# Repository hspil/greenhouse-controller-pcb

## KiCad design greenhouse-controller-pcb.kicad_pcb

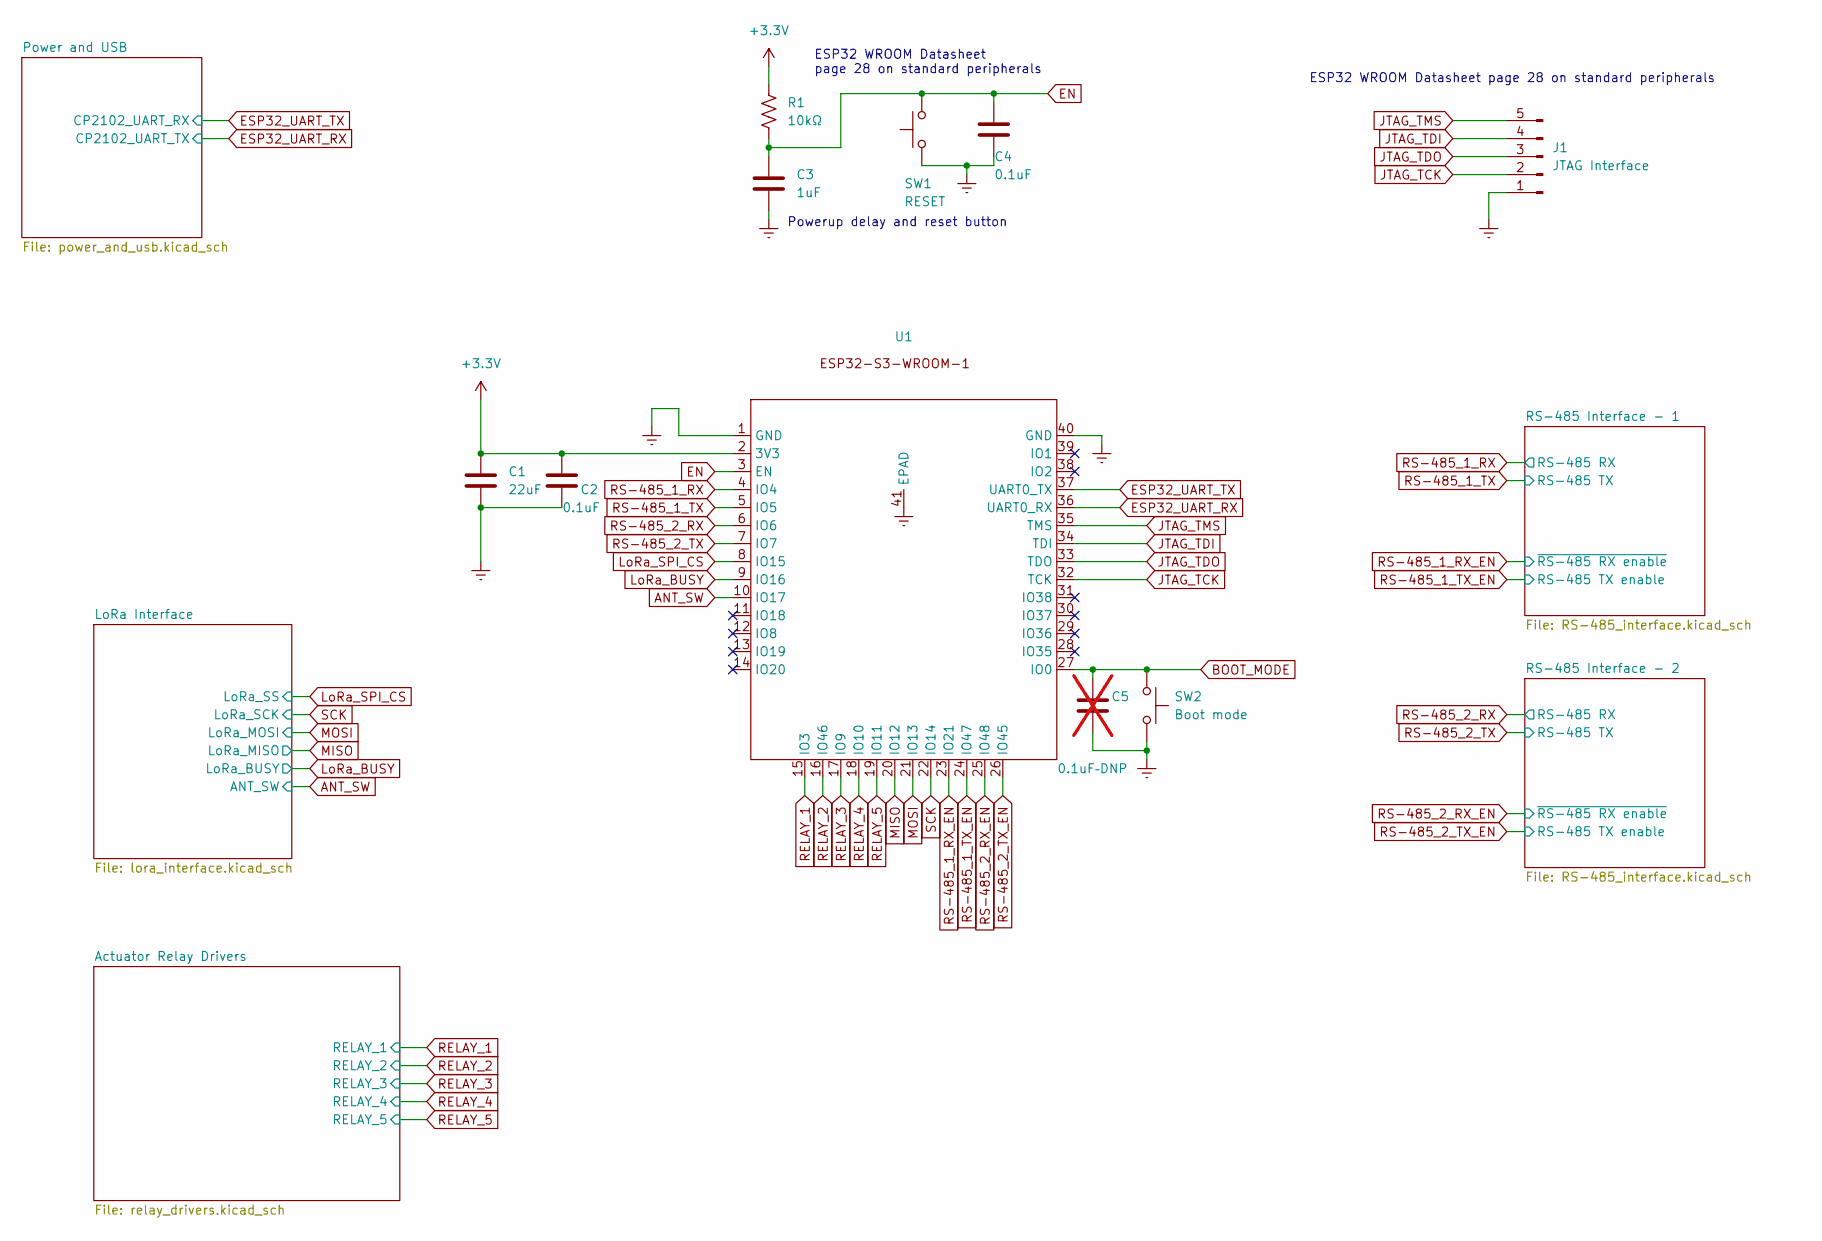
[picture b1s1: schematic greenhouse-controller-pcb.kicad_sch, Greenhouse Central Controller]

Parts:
C1: 22uF; C_0805_2012Metric_Pad1.18x1.45mm_HandSolder
C2, C4: 0.1uF; C_0805_2012Metric_Pad1.18x1.45mm_HandSolder
C3: 1uF; C_0805_2012Metric_Pad1.18x1.45mm_HandSolder
C5: 0.1uF–DNP; not fitted
J1: JTAG Interface; PinSocket_1x05_P2.54mm_Vertical
R1: 10kΩ; R_0805_2012Metric_Pad1.20x1.40mm_HandSolder
SW1: RESET; SW4_PTS815 SJM 250 SMTR LFS_CNK
SW2: Boot mode; SW4_PTS815 SJM 250 SMTR LFS_CNK
U1: ESP32-S3-WROOM-1_EXP

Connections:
+3.3V: C1.1, C2.1, R1.1, U1.2 (3V3); also elsewhere on the board
ANT_SW: U1.10 (IO17); also elsewhere on the board
BOOT_MODE: C5.1, SW2.1, U1.27 (IO0); also elsewhere on the board
ESP32_UART_RX: U1.36 (UART0_RX); also elsewhere on the board
ESP32_UART_TX: U1.37 (UART0_TX); also elsewhere on the board
JTAG_TCK: J1.2, U1.32 (TCK)
JTAG_TDI: J1.4, U1.34 (TDI)
JTAG_TDO: J1.3, U1.33 (TDO)
JTAG_TMS: J1.5, U1.35 (TMS)
LoRa_BUSY: U1.9 (IO16); also elsewhere on the board
LoRa_SPI_CS: U1.8 (IO15); also elsewhere on the board
MISO: U1.20 (IO12); also elsewhere on the board
MOSI: U1.21 (IO13); also elsewhere on the board
RELAY_1: U1.15 (IO3); also elsewhere on the board
RELAY_2: U1.16 (IO46); also elsewhere on the board
RELAY_3: U1.17 (IO9); also elsewhere on the board
RELAY_4: U1.18 (IO10); also elsewhere on the board
RELAY_5: U1.19 (IO11); also elsewhere on the board
RS-485_1_RX: U1.4 (IO4); also elsewhere on the board
RS-485_1_RX_EN: U1.23 (IO21); also elsewhere on the board
RS-485_1_TX: U1.5 (IO5); also elsewhere on the board
RS-485_1_TX_EN: U1.24 (IO47); also elsewhere on the board
RS-485_2_RX: U1.6 (IO6); also elsewhere on the board
RS-485_2_RX_EN: U1.25 (IO48); also elsewhere on the board
RS-485_2_TX: U1.7 (IO7); also elsewhere on the board
RS-485_2_TX_EN: U1.26 (IO45); also elsewhere on the board
SCK: U1.22 (IO14); also elsewhere on the board

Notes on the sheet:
Powerup delay and reset button
ESP32 WROOM Datasheet page 28 on standard peripherals
ESP32 WROOM Datasheet page 28 on standard peripherals

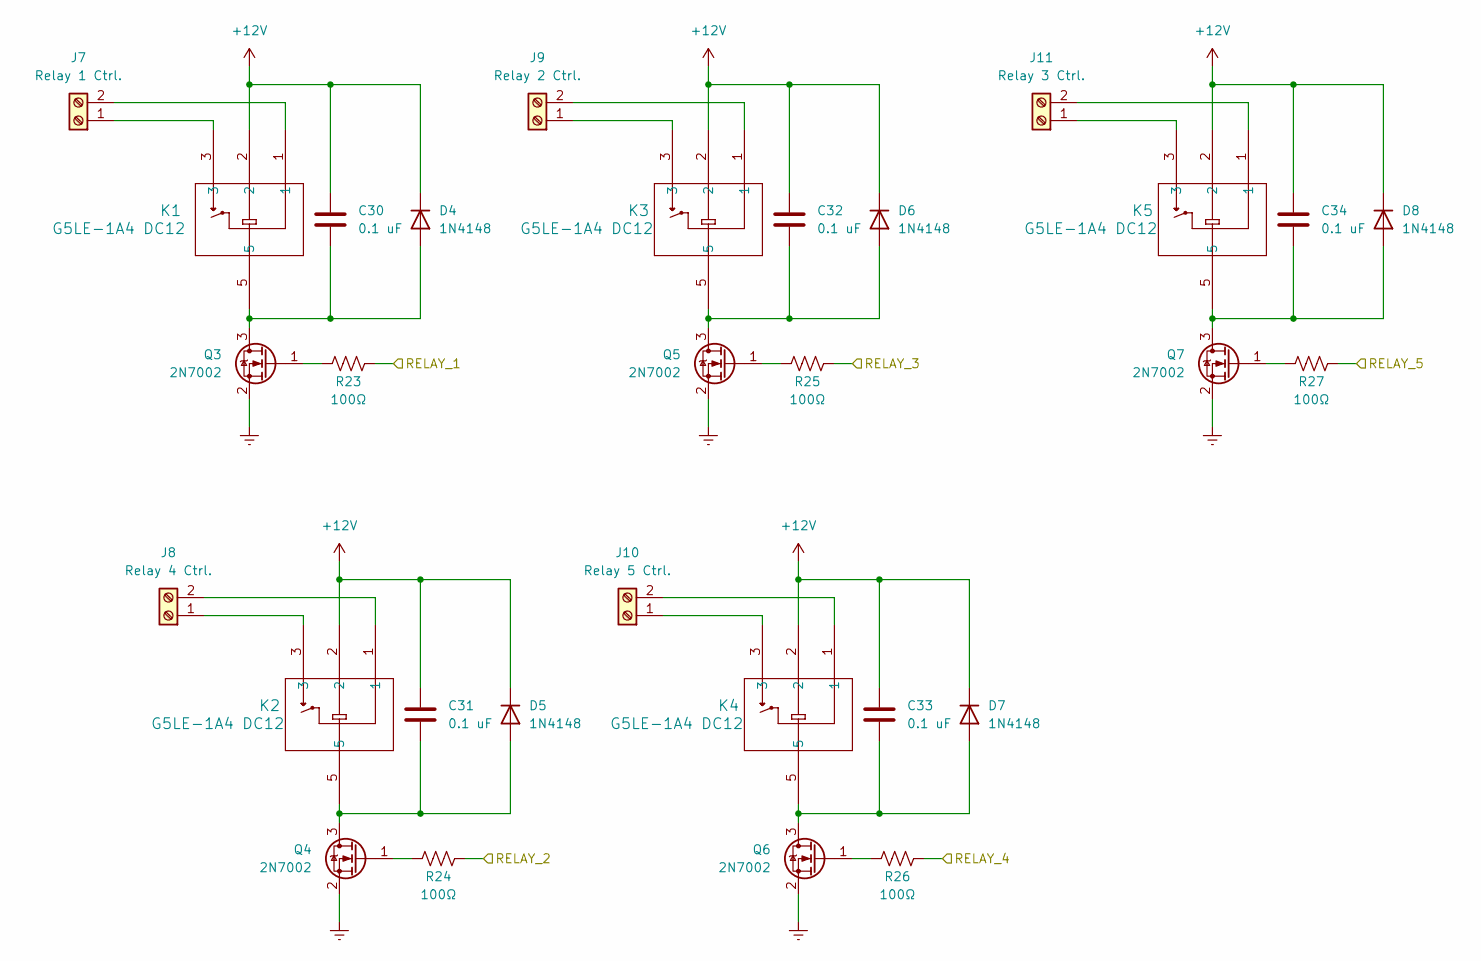
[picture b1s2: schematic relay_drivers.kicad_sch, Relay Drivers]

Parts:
C30, C31, C32, C33, C34: 0.1 uF; C_0805_2012Metric_Pad1.18x1.45mm_HandSolder
D4, D5, D6, D7, D8: 1N4148; D_DO-35_SOD27_P7.62mm_Horizontal
J7: Relay 1 Ctrl.; CUI_TB007-508-02BE
J8: Relay 4 Ctrl.; CUI_TB007-508-02BE
J9: Relay 2 Ctrl.; CUI_TB007-508-02BE
J10: Relay 5 Ctrl.; CUI_TB007-508-02BE
J11: Relay 3 Ctrl.; CUI_TB007-508-02BE
K1, K2, K3, K4, K5: G5LE-1A4 DC12; RELAY_G5LE-1A DC5_OMR
Q3, Q4, Q5, Q6, Q7: 2N7002; SOT-23
R23, R24, R25, R26, R27: 100Ω; R_0805_2012Metric_Pad1.20x1.40mm_HandSolder

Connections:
+12V: C30.1, C31.1, C32.1, C33.1, C34.1, D4.1 (K), D5.1 (K), D6.1 (K), D7.1 (K), D8.1 (K), K1.2, K2.2, K3.2, K4.2, K5.2; also elsewhere on the board
unnamed: C30.2, D4.2 (A), K1.5, Q3.3 (D)
unnamed: C31.2, D5.2 (A), K2.5, Q4.3 (D)
unnamed: C32.2, D6.2 (A), K3.5, Q5.3 (D)
unnamed: C33.2, D7.2 (A), K4.5, Q6.3 (D)
unnamed: C34.2, D8.2 (A), K5.5, Q7.3 (D)
unnamed: J7.1, K1.3
unnamed: J7.2, K1.1
unnamed: J8.1, K2.3
unnamed: J8.2, K2.1
unnamed: J9.1, K3.3
unnamed: J9.2, K3.1
unnamed: J10.1, K4.3
unnamed: J10.2, K4.1
unnamed: J11.1, K5.3
unnamed: J11.2, K5.1
unnamed: Q3.1 (G), R23.2
unnamed: Q4.1 (G), R24.1
unnamed: Q5.1 (G), R25.1
unnamed: Q6.1 (G), R26.1
unnamed: Q7.1 (G), R27.1
RELAY_1: R23.1; also elsewhere on the board
RELAY_2: R24.2; also elsewhere on the board
RELAY_3: R25.2; also elsewhere on the board
RELAY_4: R26.2; also elsewhere on the board
RELAY_5: R27.2; also elsewhere on the board

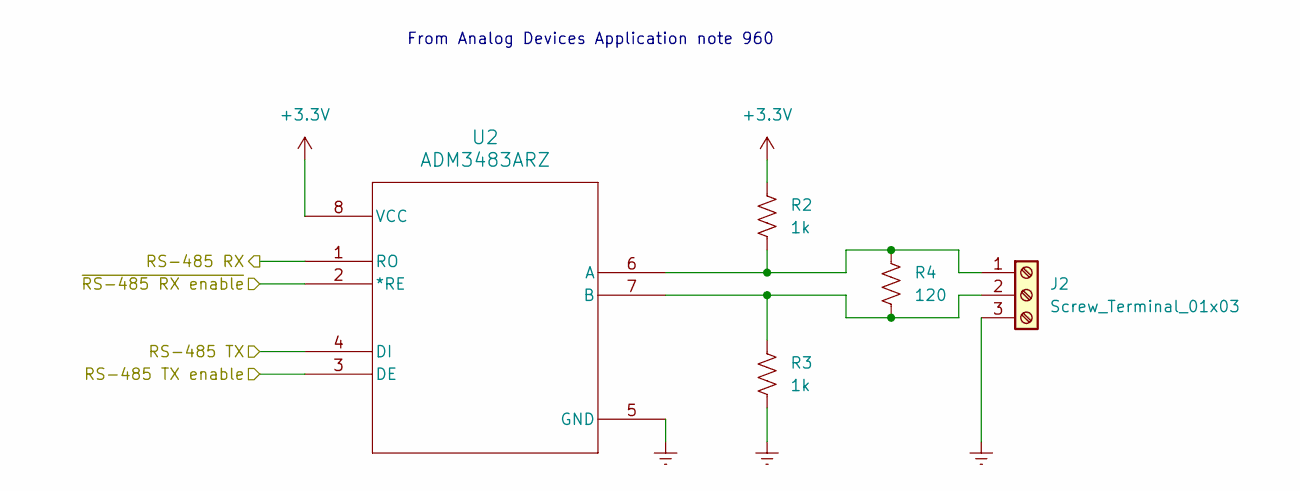
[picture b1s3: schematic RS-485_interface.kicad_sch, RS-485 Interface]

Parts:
J2: Screw_Terminal_01x03; CUI_TB007-508-03BE
R2, R3: 1k; R_0805_2012Metric_Pad1.20x1.40mm_HandSolder
R4: 120; R_Axial_DIN0207_L6.3mm_D2.5mm_P7.62mm_Horizontal
U2: ADM3483ARZ; R_8_ADI

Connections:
+3.3V: R2.1, U2.8 (VCC); also elsewhere on the board
unnamed: J2.1, R2.2, R4.1, U2.6 (A)
unnamed: J2.2, R3.1, R4.2, U2.7 (B)
RS-485_1_RX: U2.1 (RO); also elsewhere on the board
RS-485_1_RX_EN: U2.2 (*RE); also elsewhere on the board
RS-485_1_TX: U2.4 (DI); also elsewhere on the board
RS-485_1_TX_EN: U2.3 (DE); also elsewhere on the board

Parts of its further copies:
J3: Screw_Terminal_01x03; CUI_TB007-508-03BE
R5, R6: 1k; R_0805_2012Metric_Pad1.20x1.40mm_HandSolder
R7: 120; R_Axial_DIN0207_L6.3mm_D2.5mm_P7.62mm_Horizontal
U3: ADM3483ARZ; R_8_ADI

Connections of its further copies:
+3.3V: R5.1, U3.8 (VCC); also elsewhere on the board
unnamed: J3.1, R5.2, R7.1, U3.6 (A)
unnamed: J3.2, R6.1, R7.2, U3.7 (B)
RS-485_2_RX: U3.1 (RO); also elsewhere on the board
RS-485_2_RX_EN: U3.2 (*RE); also elsewhere on the board
RS-485_2_TX: U3.4 (DI); also elsewhere on the board
RS-485_2_TX_EN: U3.3 (DE); also elsewhere on the board

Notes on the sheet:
From Analog Devices Application note 960

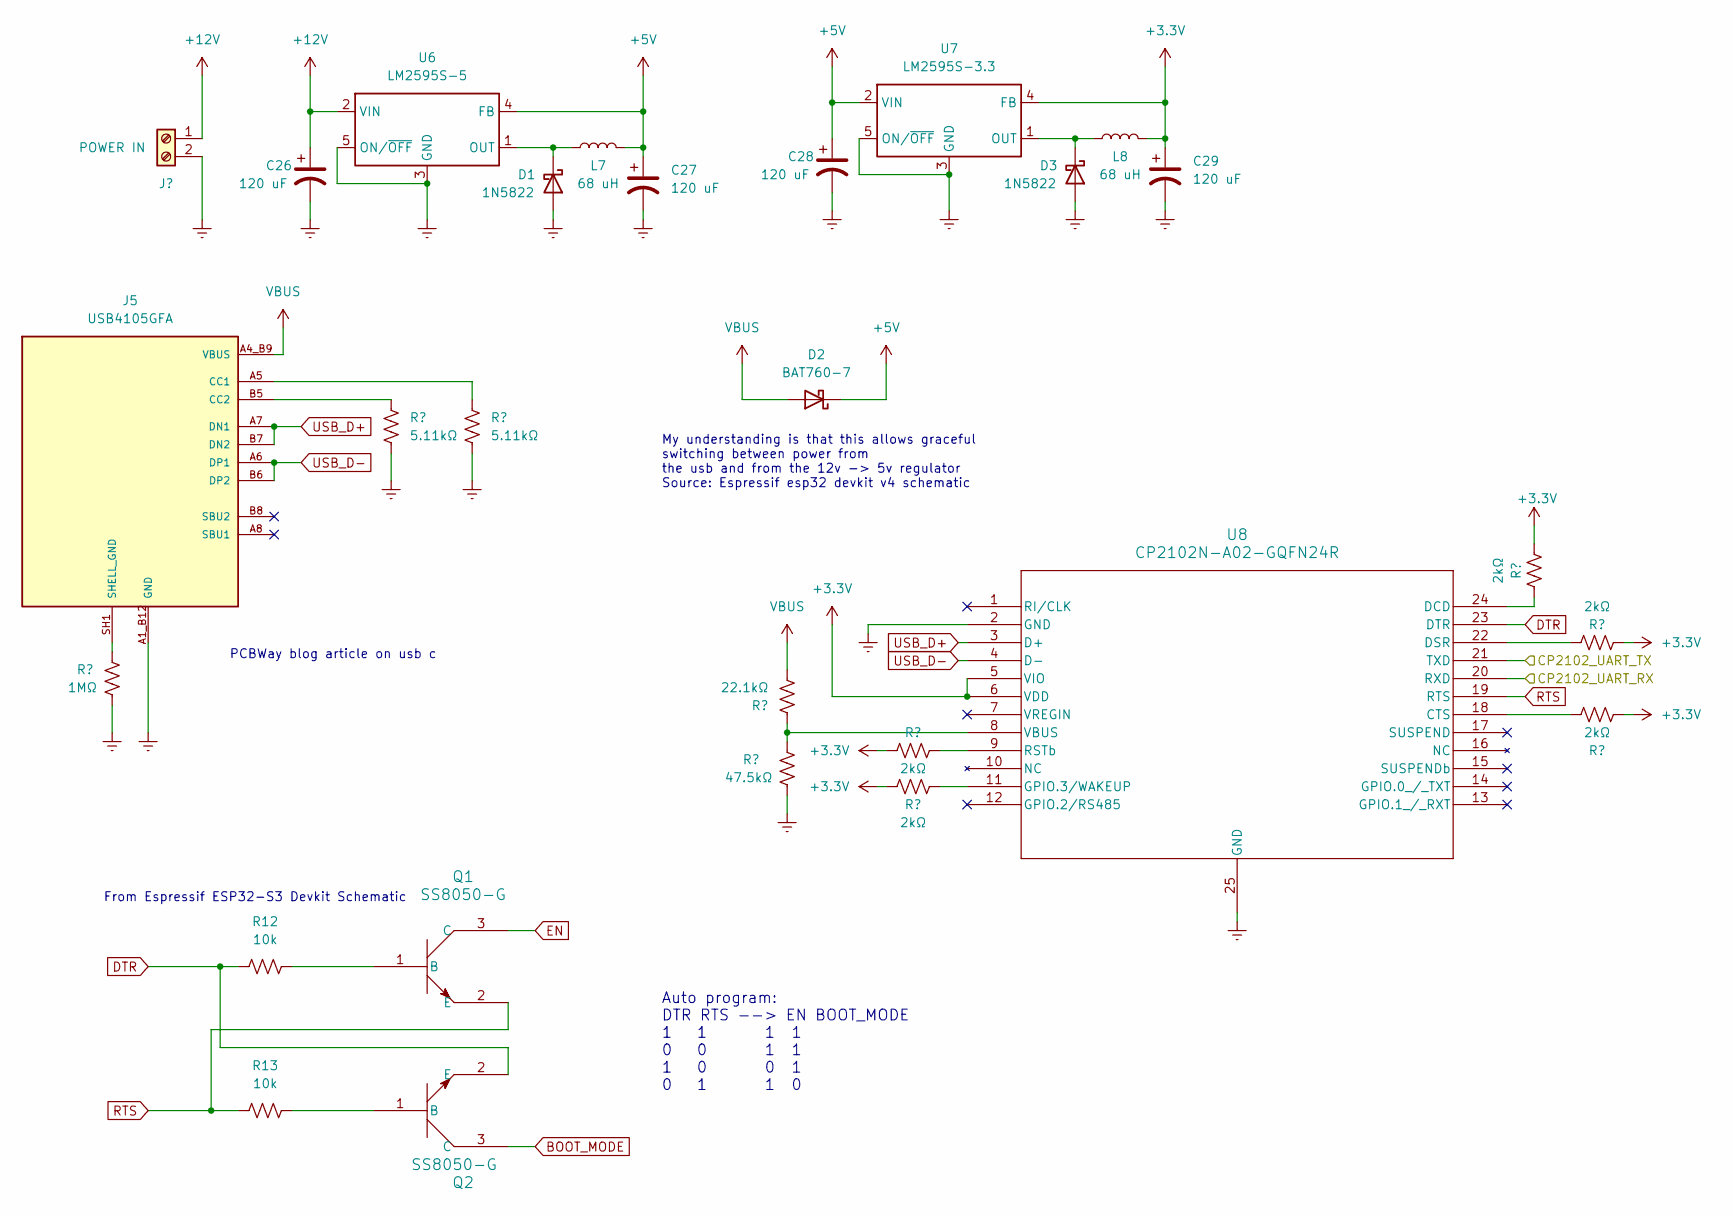
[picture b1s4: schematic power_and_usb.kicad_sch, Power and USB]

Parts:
C26, C27, C28, C29: 120 uF; CAP_EEEFNV121XUP
D1, D3: 1N5822; D_DO-201AD_P15.24mm_Horizontal
D2: BAT760-7; SOD2513X120N
J5: USB4105GFA; GCT_USB4105GFA; PARTREV B3
J6: POWER IN; CUI_TB007-508-02BE
L7, L8: 68 uH; L_0805_2012Metric_Pad1.15x1.40mm_HandSolder
Q1, Q2: SS8050-G; TRAN_SS8050-G_CIP
R11: 1MΩ; R_0805_2012Metric_Pad1.20x1.40mm_HandSolder
R12, R13: 10k; R_0805_2012Metric_Pad1.20x1.40mm_HandSolder
R14, R15: 5.11kΩ; R_0805_2012Metric_Pad1.20x1.40mm_HandSolder
R16: 22.1kΩ; R_0805_2012Metric_Pad1.20x1.40mm_HandSolder
R17: 47.5kΩ; R_0805_2012Metric_Pad1.20x1.40mm_HandSolder
R18, R19, R20, R21, R22: 2kΩ; R_0805_2012Metric_Pad1.20x1.40mm_HandSolder
U6: LM2595S-5; TO-263-5_TabPin3
U7: LM2595S-3.3; TO-263-5_TabPin3
U8: CP2102N-A02-GQFN24R; QFN24_SIL

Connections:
+3.3V: C29.1, L8.2, R18.1, R19.1, R20.1, R21.1, R22.1, U7.4 (FB), U8.5 (VIO), U8.6 (VDD); also elsewhere on the board
+5V: C27.1, C28.1, D2.2 (K), L7.2, U6.4 (FB), U7.2 (VIN)
+12V: C26.1, J6.1, U6.2 (VIN); also elsewhere on the board
BOOT_MODE: Q2.3 (C); also elsewhere on the board
DTR: Q2.2 (E), R12.1, U8.23 (DTR)
ESP32_UART_RX: U8.21 (TXD); also elsewhere on the board
ESP32_UART_TX: U8.20 (RXD); also elsewhere on the board
unnamed: D1.1 (K), L7.1, U6.1 (OUT)
unnamed: D3.1 (K), L8.1, U7.1 (OUT)
unnamed: J5.A5 (CC1), R15.1
unnamed: J5.B5 (CC2), R14.1
unnamed: J5.SH1 (SHELL_GND), R11.1
unnamed: Q1.1 (B), R12.2
unnamed: Q2.1 (B), R13.2
unnamed: R22.2, U8.18 (CTS)
unnamed: R20.2, U8.24 (DCD)
unnamed: R21.2, U8.22 (DSR)
unnamed: R19.2, U8.11 (GPIO.3/WAKEUP)
unnamed: R18.2, U8.9 (RSTb)
unnamed: R16.1, R17.1, U8.8 (VBUS)
RTS: Q1.2 (E), R13.1, U8.19 (RTS)
USB_D+: J5.A7 (DN1), J5.B7 (DN2), U8.3 (D+)
USB_D-: J5.A6 (DP1), J5.B6 (DP2), U8.4 (D-)
VBUS: D2.1 (A), J5.A4_B9 (VBUS), J5.B4_A9, R16.2

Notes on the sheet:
My understanding is that this allows graceful switching between power from the usb and from the 12v -> 5v regulator Source: Espressif esp32 devkit v4 schematic
From Espressif ESP32-S3 Devkit Schematic
Auto program: DTR RTS --> EN BOOT_MODE 1 1 1 1 0 0 1 1 1 0 0 1 0 1 1 0
PCBWay blog article on usb c

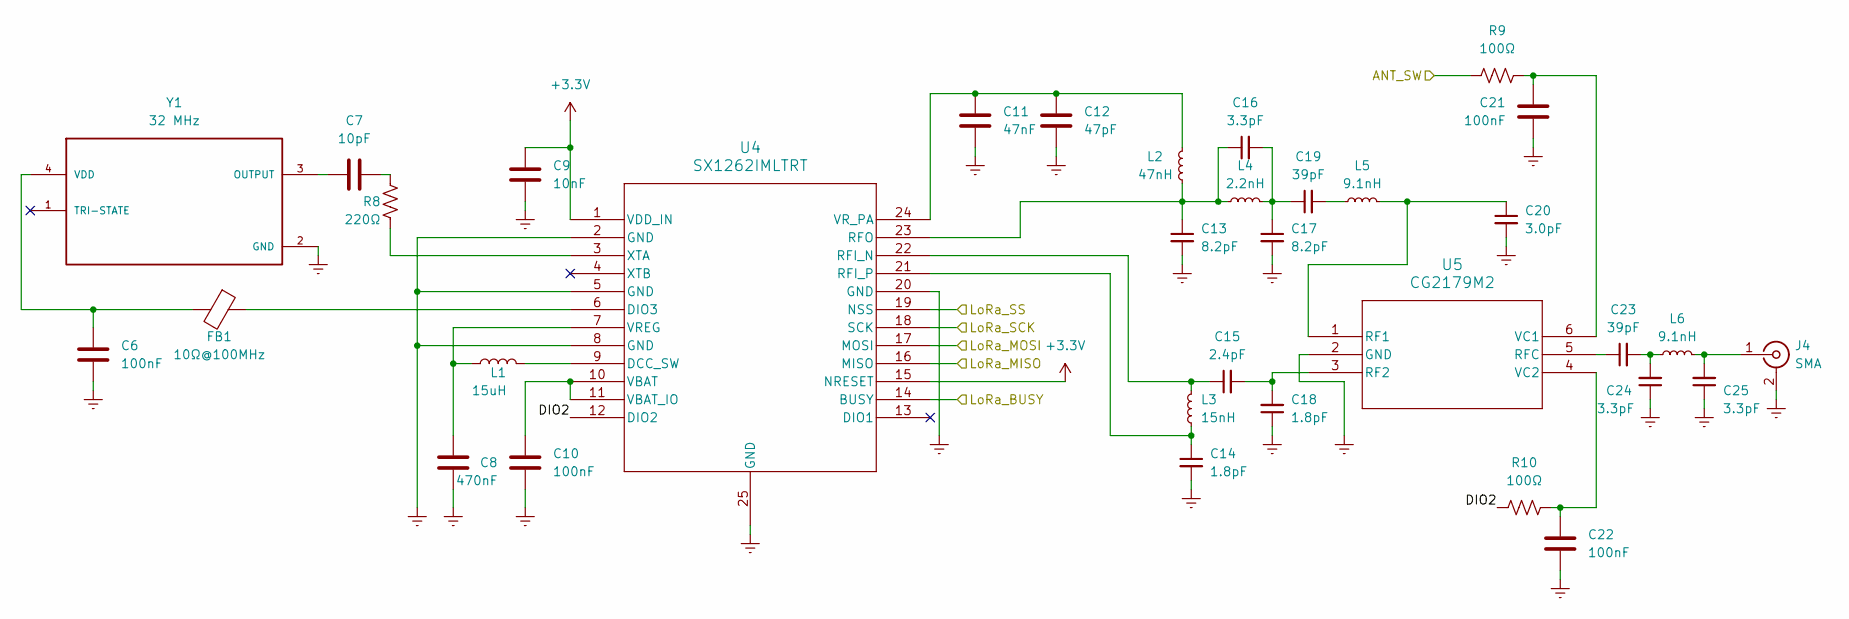
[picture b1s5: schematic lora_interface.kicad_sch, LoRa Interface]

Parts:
C6, C10: 100nF; C_0402_1005Metric_Pad0.74x0.62mm_HandSolder
C7: 10pF; C_0402_1005Metric_Pad0.74x0.62mm_HandSolder
C8: 470nF; C_0402_1005Metric_Pad0.74x0.62mm_HandSolder
C9: 10nF; C_0402_1005Metric_Pad0.74x0.62mm_HandSolder
C11: 47nF; C_0402_1005Metric_Pad0.74x0.62mm_HandSolder
C12: 47pF; C_0402_1005Metric_Pad0.74x0.62mm_HandSolder
C13, C17: 8.2pF; C_0402_1005Metric_Pad0.74x0.62mm_HandSolder
C14, C18: 1.8pF; C_0402_1005Metric_Pad0.74x0.62mm_HandSolder
C15: 2.4pF; C_0402_1005Metric_Pad0.74x0.62mm_HandSolder
C16, C24, C25: 3.3pF; C_0402_1005Metric_Pad0.74x0.62mm_HandSolder
C19, C23: 39pF; C_0402_1005Metric_Pad0.74x0.62mm_HandSolder
C20: 3.0pF; C_0402_1005Metric_Pad0.74x0.62mm_HandSolder
C21, C22: 100nF; C_0805_2012Metric_Pad1.18x1.45mm_HandSolder
FB1: 10Ω@100MHz; L_0402_1005Metric_Pad0.77x0.64mm_HandSolder
J4: SMA; SMA_Samtec_SMA-J-P-X-ST-EM1_EdgeMount
L1: 15uH; L_0402_1005Metric_Pad0.77x0.64mm_HandSolder
L2: 47nH; L_0402_1005Metric_Pad0.77x0.64mm_HandSolder
L3: 15nH; L_0402_1005Metric_Pad0.77x0.64mm_HandSolder
L4: 2.2nH; L_0402_1005Metric_Pad0.77x0.64mm_HandSolder
L5, L6: 9.1nH; L_0402_1005Metric_Pad0.77x0.64mm_HandSolder
R8: 220Ω; R_0402_1005Metric_Pad0.72x0.64mm_HandSolder
R9, R10: 100Ω; R_0805_2012Metric_Pad1.20x1.40mm_HandSolder
U4: SX1262IMLTRT; QFN24_4X4_SEM
U5: CG2179M2; MINISO6_CG21_CEL
Y1: 32 MHz; OSC_ECS-TXO-2520-33-320-AN-TR; PARTREV 2017

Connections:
+3.3V: C9.1, U4.1 (VDD_IN), U4.15 (NRESET); also elsewhere on the board
/LoRa Interface/DIO2: R10.1, U4.12 (DIO2)
ANT_SW: R9.1; also elsewhere on the board
LoRa_BUSY: U4.14 (BUSY); also elsewhere on the board
LoRa_SPI_CS: U4.19 (NSS); also elsewhere on the board
MISO: U4.16 (MISO); also elsewhere on the board
MOSI: U4.17 (MOSI); also elsewhere on the board
unnamed: C7.2, R8.1
unnamed: C16.2, C17.1, C19.1, L4.2
unnamed: C19.2, L5.1
unnamed: C23.2, C24.2, L6.1
unnamed: C25.2, J4.1 (In), L6.2
unnamed: L1.2, U4.9 (DCC_SW)
unnamed: FB1.1, U4.6 (DIO3)
unnamed: C15.1, L3.2, U4.22 (RFI_N)
unnamed: C14.1, L3.1, U4.21 (RFI_P)
unnamed: C13.1, C16.1, L2.1, L4.1, U4.23 (RFO)
unnamed: C10.1, U4.10 (VBAT), U4.11 (VBAT_IO)
unnamed: C8.1, L1.1, U4.7 (VREG)
unnamed: C11.1, C12.1, L2.2, U4.24 (VR_PA)
unnamed: R8.2, U4.3 (XTA)
unnamed: C20.1, L5.2, U5.1 (RF1)
unnamed: C15.2, C18.2, U5.3 (RF2)
unnamed: C23.1, U5.5 (RFC)
unnamed: C21.1, R9.2, U5.6 (VC1)
unnamed: C22.1, R10.2, U5.4 (VC2)
unnamed: C7.1, Y1.3 (OUTPUT)
unnamed: C6.1, FB1.2, Y1.4 (VDD)
SCK: U4.18 (SCK); also elsewhere on the board

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
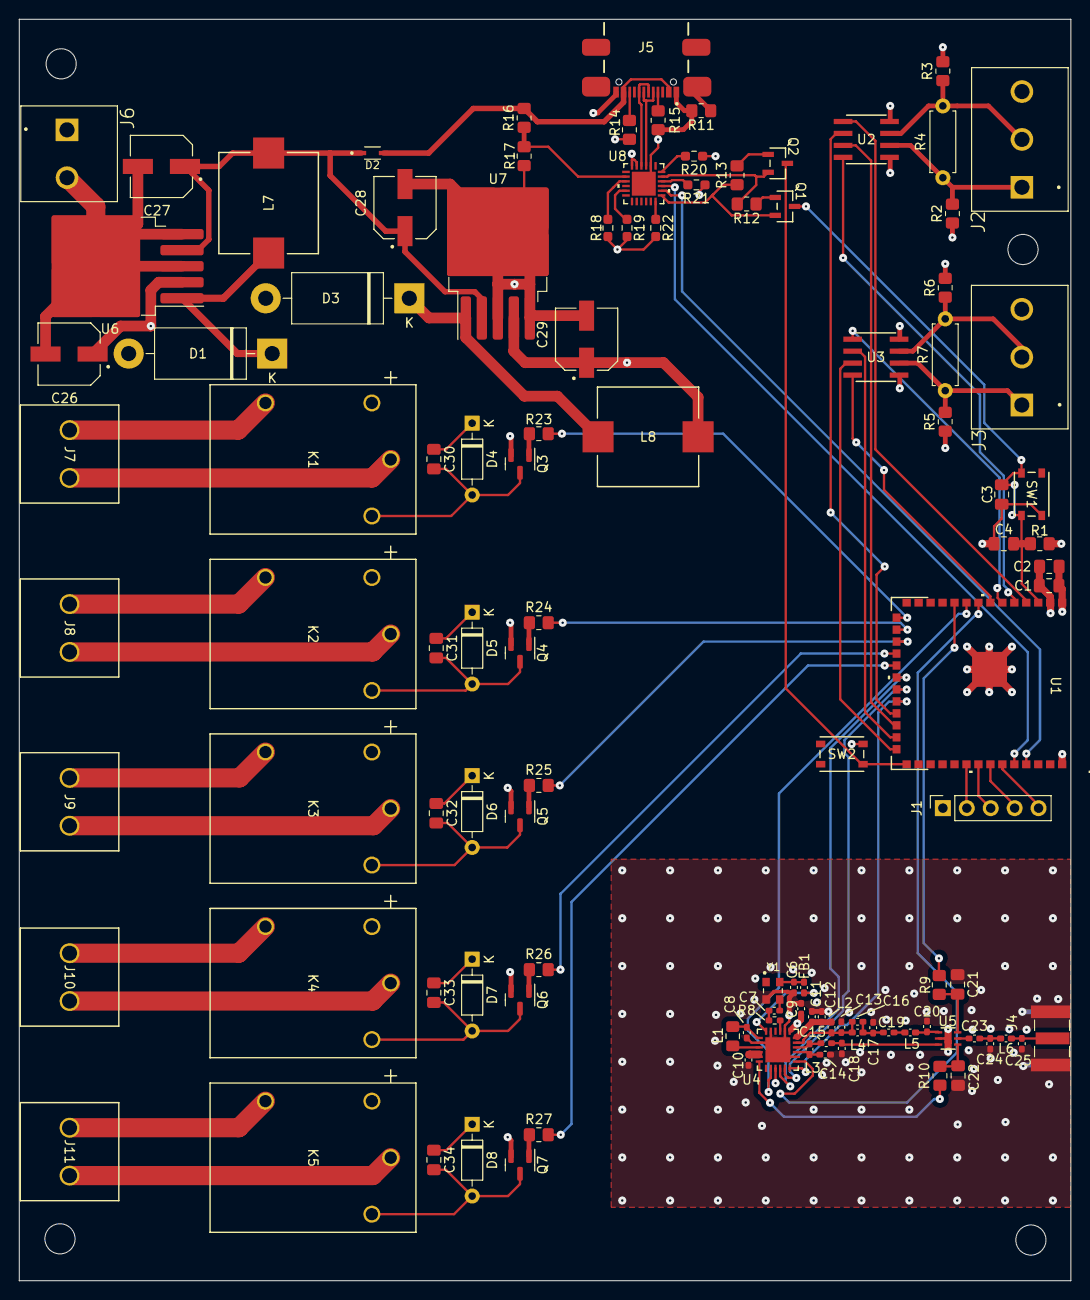
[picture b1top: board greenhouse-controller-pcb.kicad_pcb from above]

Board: 4 copper layers, 111.6 x 133.9 mm, 111 parts (0 on the bottom side), 95 nets.

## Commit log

2023-10-11 improved .gitignore courtesy of github
2023-10-11 spring cleaning
2023-11-01 version 1
2025-02-27 unknown latest changes
